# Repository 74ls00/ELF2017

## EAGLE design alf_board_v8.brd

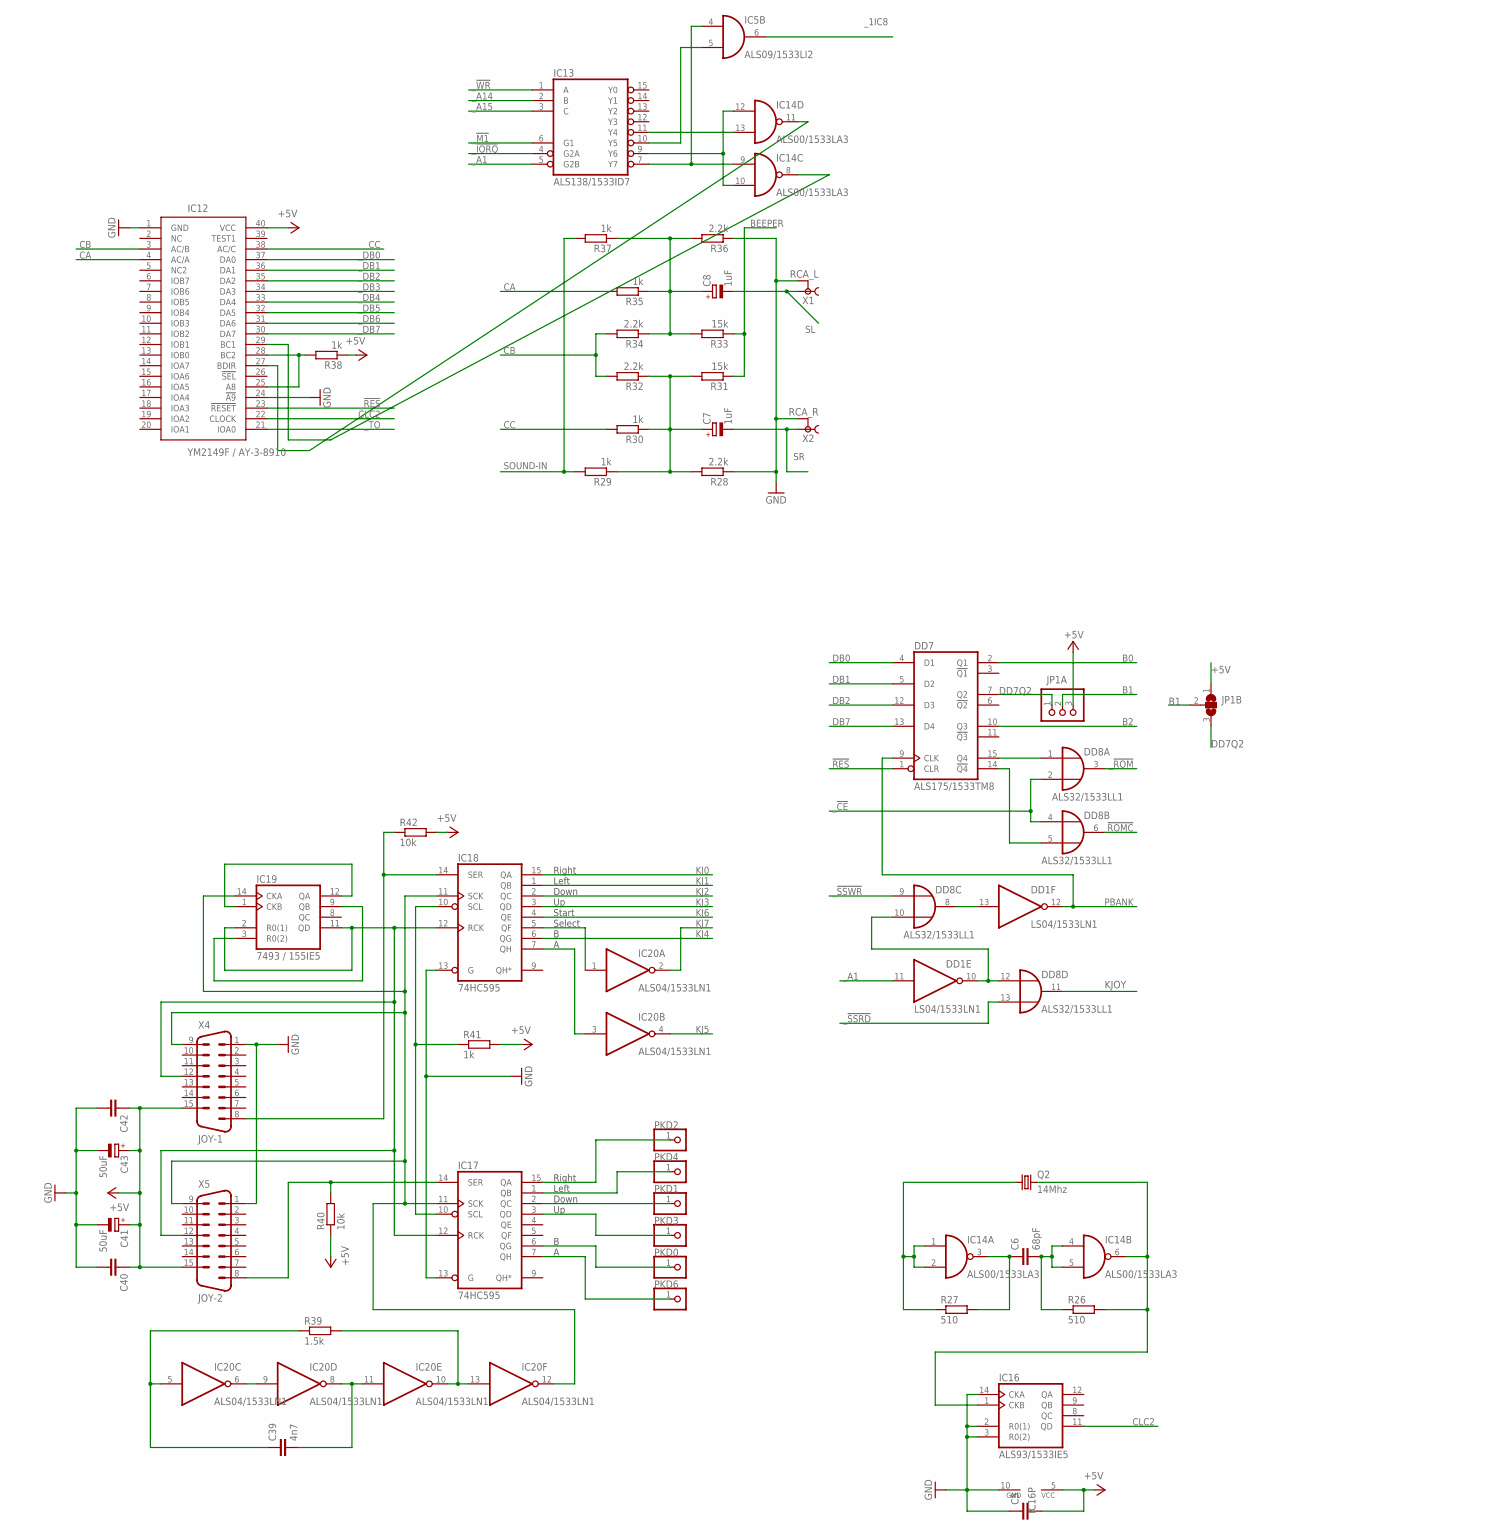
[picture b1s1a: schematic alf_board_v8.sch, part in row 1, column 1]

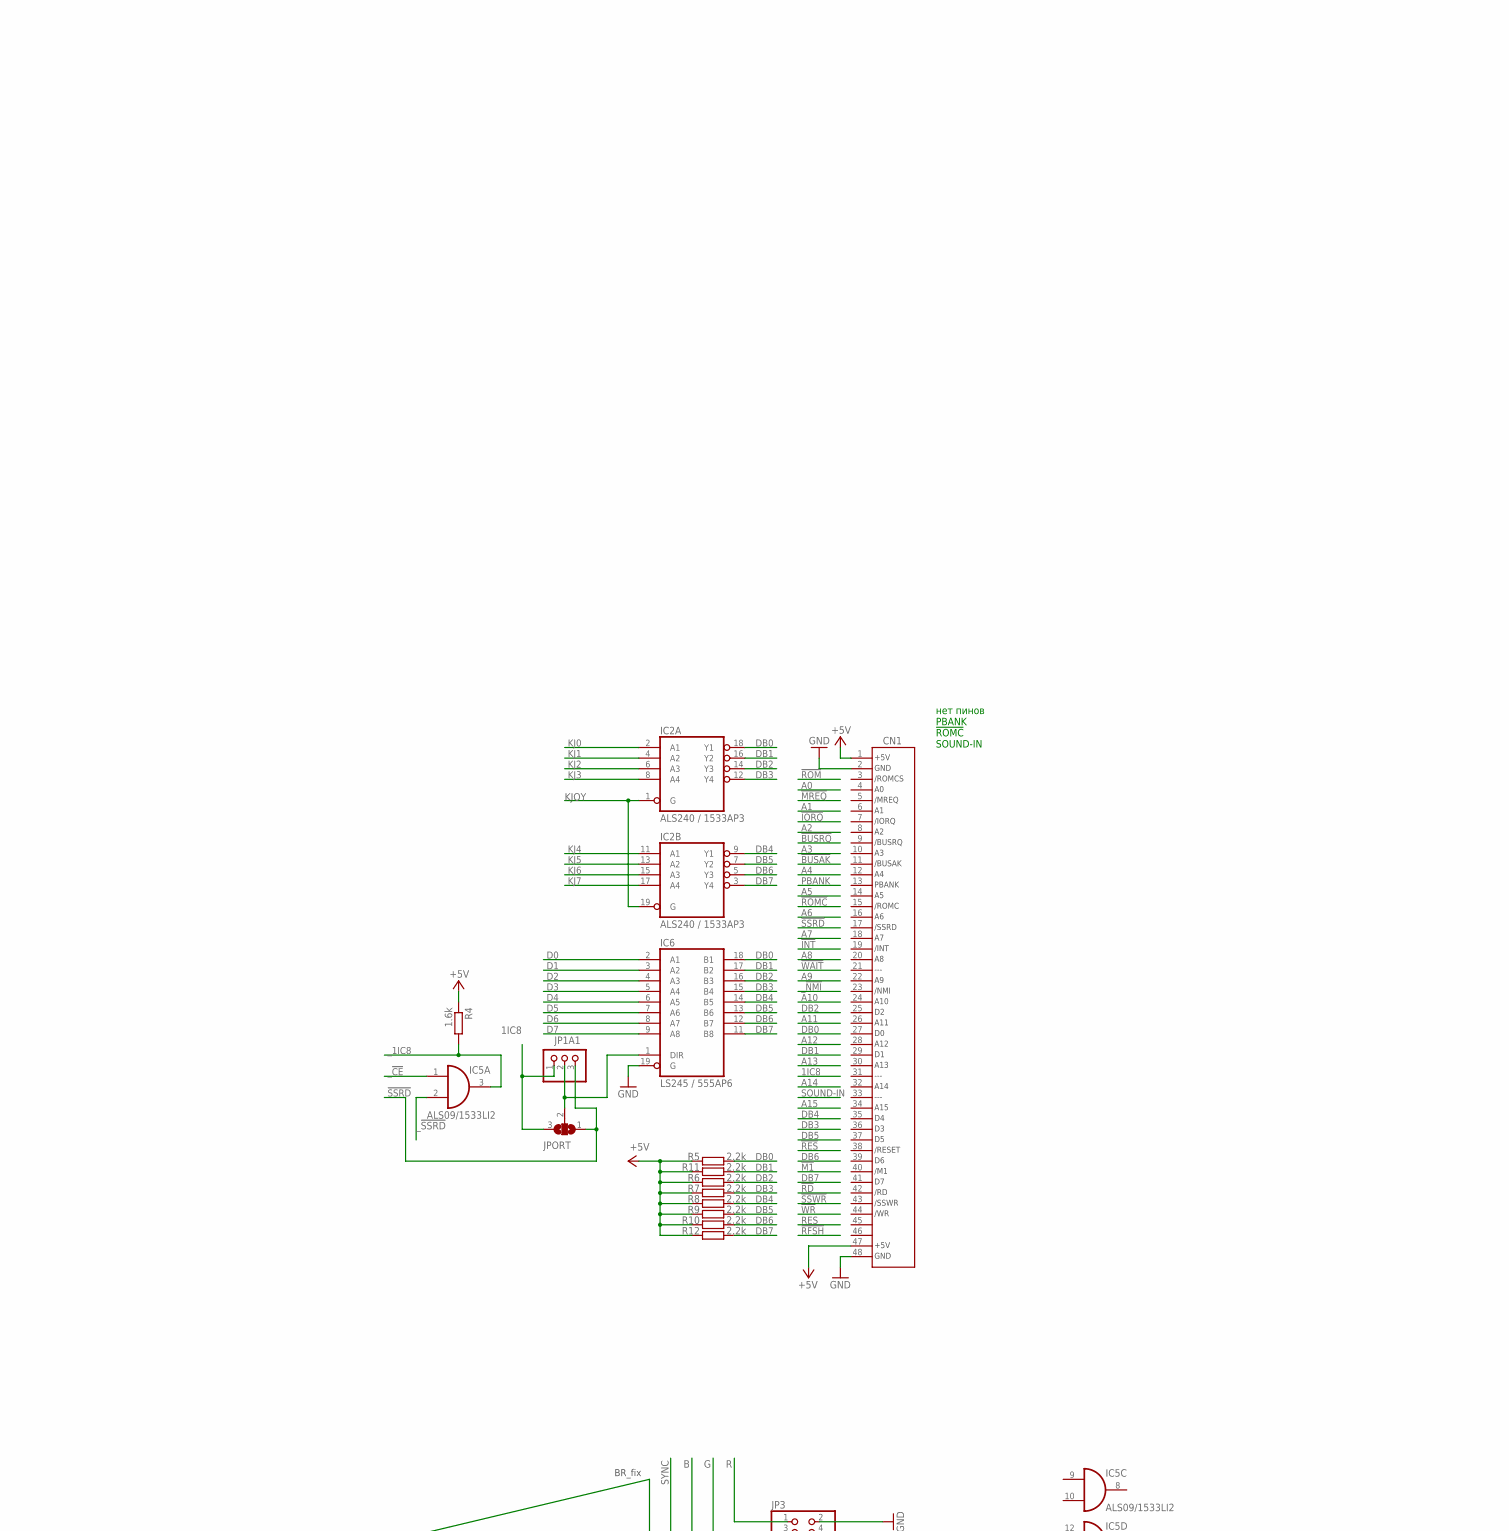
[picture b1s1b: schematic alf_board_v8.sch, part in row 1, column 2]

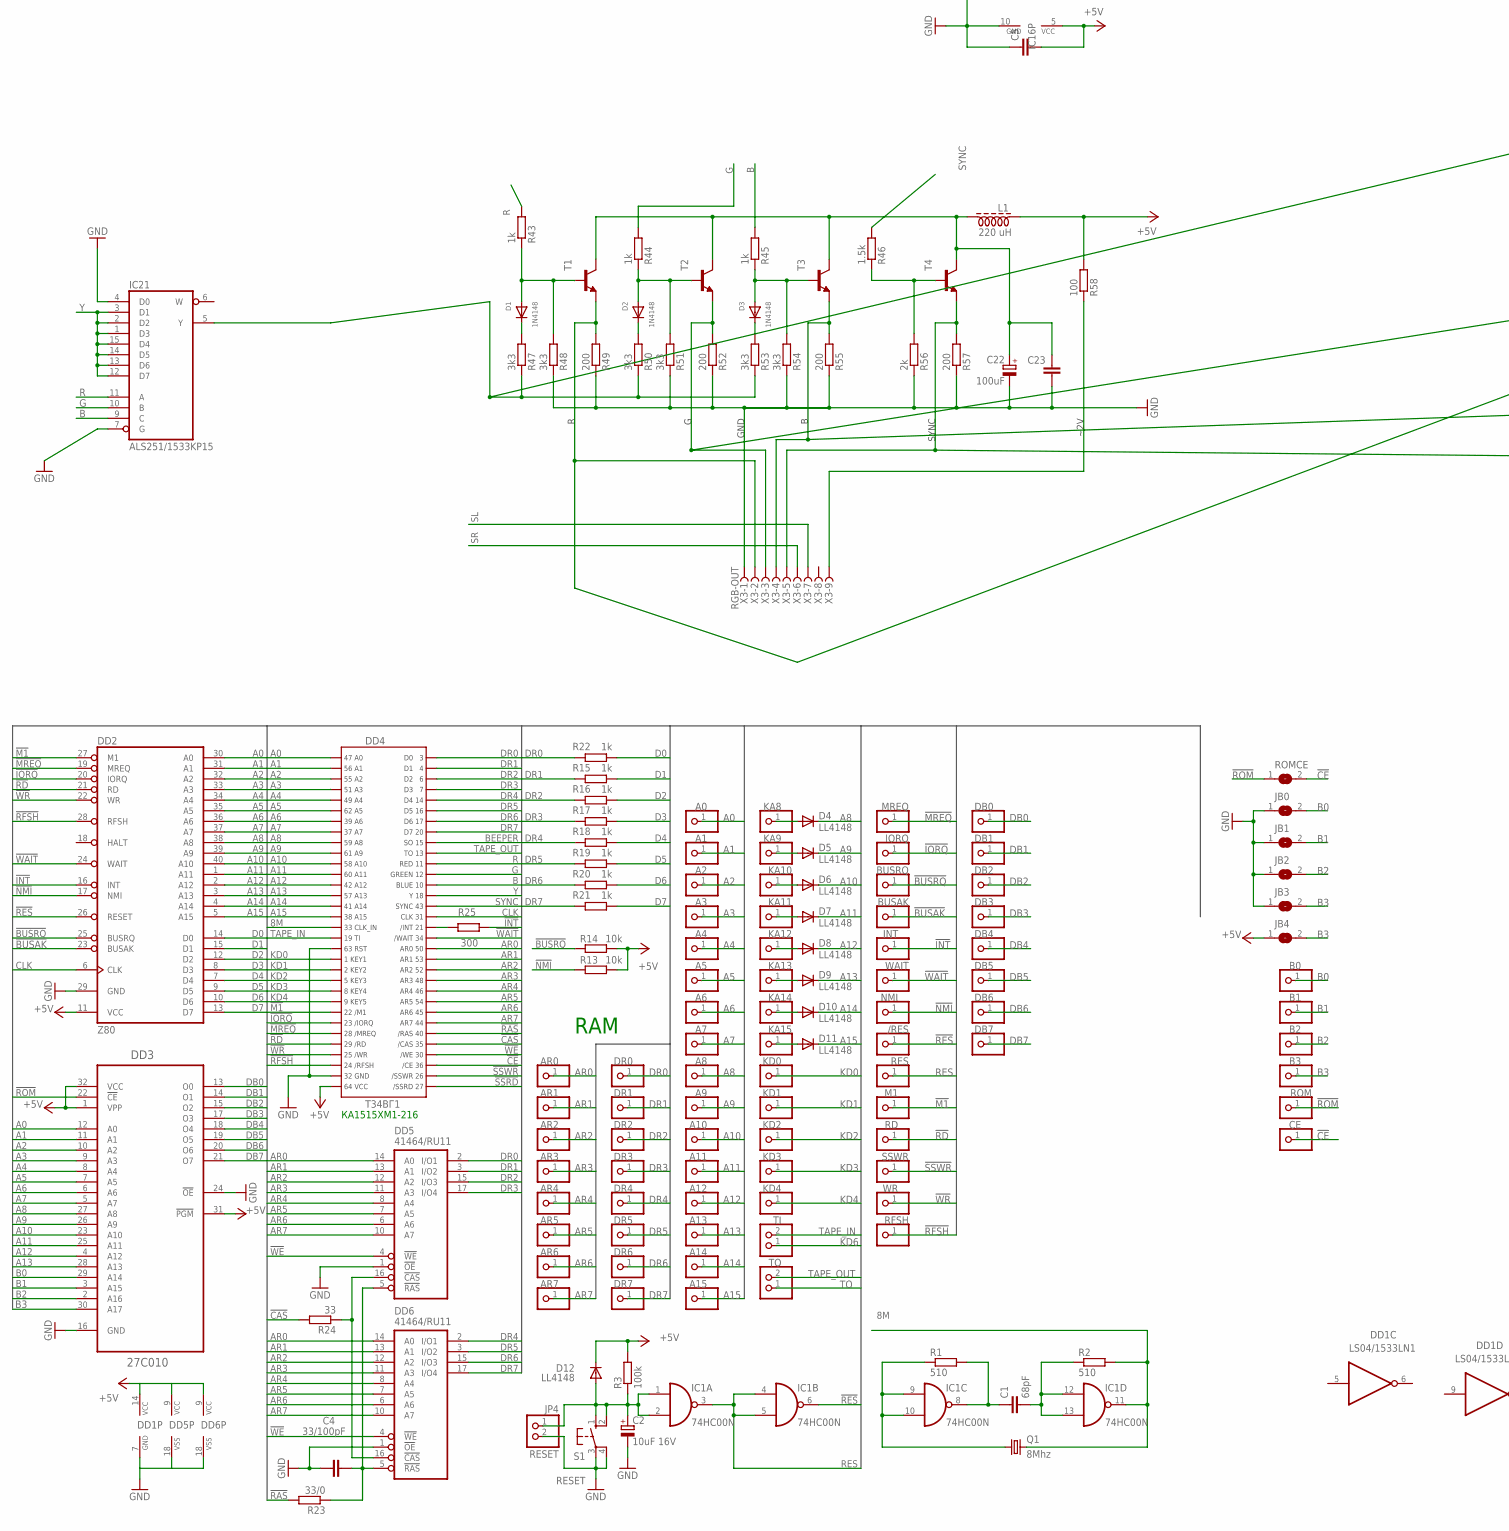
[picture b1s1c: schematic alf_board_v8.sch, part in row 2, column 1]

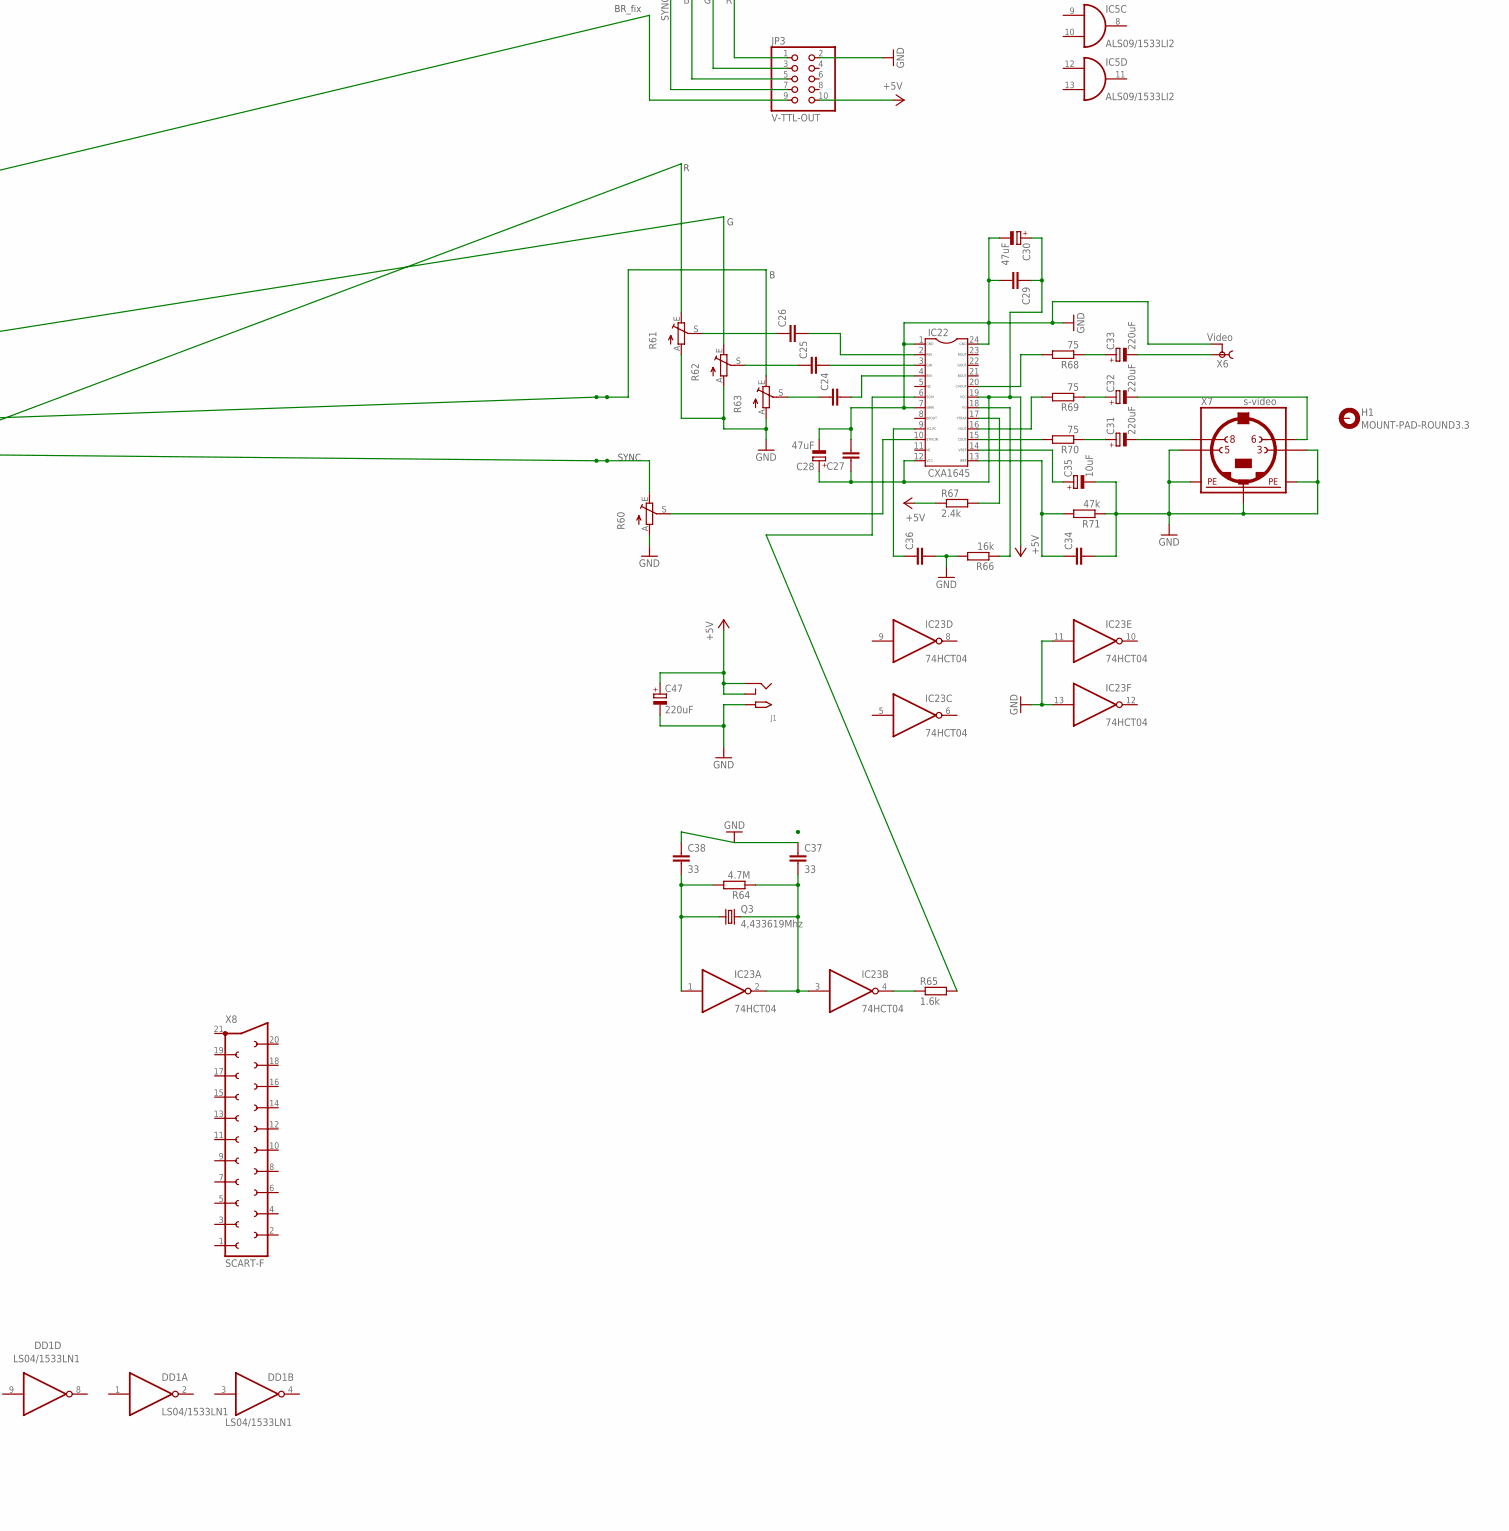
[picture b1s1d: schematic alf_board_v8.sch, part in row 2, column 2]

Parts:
/RES: PINHD-1X1; 1X01
A0, A1, A2, A3, A4, A5, A6, A7, A8, A9, A10, A11, A12, A13, A14, A15: PINHD-1X1; 1X01
AR0, AR1, AR2, AR3, AR4, AR5, AR6, AR7: PINHD-1X1; 1X01
B0, B1, B2, B3: PINHD-1X1; 1X01
BUSAK: PINHD-1X1; 1X01
BUSRQ: PINHD-1X1; 1X01
C1, C6: 68pF; C0805
C2: 10uF 16V; SMC_A; MPN MCNP35V106M5X11
C4: 33/100pF; C102-043X133
C5, C23, C24, C25, C26, C27, C29, C34, C36, C40, C42: C-EUC0805; C0805
C7, C8: 1uF; SMC_A
C22: 100uF; SMC_B
C28, C30: 47uF; SMC_B
C31, C32, C33, C47: 220uF; SMC_D
C35: 10uF; SMC_A
C37, C38: 33; C0805
C39: 4n7; C0805
C41, C43: 50uF; SMC_B
CE: PINHD-1X1; 1X01
CN1: СНП15-48
D1, D2, D3: 1N4148; DO-1N4148
D4, D5, D6, D7, D8, D9, D10, D11, D12: LL4148; SOD80C
DB0, DB1, DB2, DB3, DB4, DB5, DB6, DB7: PINHD-1X1; 1X01
DD1: LS04/1533LN1; DIL14
DD2: Z80; DIL40
DD3: 27C010; DIP254P1524X482-32P; MPN AT27C020-90PU
DD4: Т34ВГ1; TQFP64-MF
DD5, DD6: 41464/RU11; DIL18
DD7: ALS175/1533TM8; DIL16
DD8: ALS32/1533LL1; DIL14
DR0, DR1, DR2, DR3, DR4, DR5, DR6, DR7: PINHD-1X1; 1X01
H1: MOUNT-PAD-ROUND3.3; 3,3-PAD
IC1: 74HC00N; DIL14
IC2: ALS240 / 1533AP3; DIL20
IC5: ALS09/1533LI2; DIL14
IC6: LS245 / 555AP6; SO20W
IC12: YM2149F / AY-3-8910; DIL40
IC13: ALS138/1533ID7; DIL16
IC14: ALS00/1533LA3; DIL14
IC16: ALS93/1533IE5; DIL14
IC17, IC18: 74HC595; DIL16
IC19: 7493 / 155IE5; DIL14
IC20: ALS04/1533LN1; DIL14
IC21: ALS251/1533KP15; DIL16
IC22: CXA1645; SOP24
IC23: 74HCT04; DIL14
INT: PINHD-1X1; 1X01
IORQ: PINHD-1X1; 1X01
J1: 2.1MMJACKTHM; PJ-102A
JB0, JB1, JB2, JB3, JB4: SJ
JP1A, JP1A1: PINHD-1X3; 1X03
JP1B: SJ2W; SJ_2
JP3: V-TTL-OUT; 2X05
JP4: RESET; 1X02
JPORT: SJ2W; SJ_2
KA8, KA9, KA10, KA11, KA12, KA13, KA14, KA15: PINHD-1X1; 1X01
KD0, KD1, KD2, KD3, KD4: PINHD-1X1; 1X01
L1: 220 uH; Z27/24
M1: PINHD-1X1; 1X01
MREQ: PINHD-1X1; 1X01
NMI: PINHD-1X1; 1X01
PKD0, PKD1, PKD2, PKD3, PKD4, PKD6: PINHD-1X1; 1X01
Q1: 8Mhz; HC49/S; MPN HC49SM-3.6864-30-50-60-16-ATF
Q2: 14Mhz; HC49/S; MPN HC49SM-3.6864-30-50-60-16-ATF
Q3: 4,433619Mhz; HC49/S; MPN HC49SM-3.6864-30-50-60-16-ATF
R1, R2, R26, R27: 510; R0805
R3: 100k; R0805
R4, R65: 1.6k; R0805
R5, R6, R7, R8, R9, R10, R11, R12, R28, R32, R34, R36: 2.2k; R0805
R13, R14, R40, R42: 10k; R0805
R15, R16, R17, R18, R19, R20, R21, R22, R29, R30, R35, R37, R38, R41, R43, R44, R45: 1k; R0805
R23: 33/0; 0207/12
R24: 33; 0207/10
R25: 300; R0805
R31, R33: 15k; R0805
R39, R46: 1.5k; R0805
R47, R48, R50, R51, R53, R54: 3k3; R0805
R49, R52, R55, R57: 200; R0805
R56: 2k; R0805
R58: 100; R0805
R60, R61, R62, R63: TRIM_EU-CA6V; CA6V
R64: 4.7M; R0805
R66: 16k; R0805
R67: 2.4k; R0805
R68, R69, R70: 75; R0805
R71: 47k; R0805
RD: PINHD-1X1; 1X01
RES: PINHD-1X1; 1X01
RFSH: PINHD-1X1; 1X01
ROM: PINHD-1X1; 1X01
ROMCE: SJ
S1: RESET; B3F-10XX
SSWR: PINHD-1X1; 1X01
T1, T2, T3, T4: BC549-NPN-TO92-CBE; TO92-CBE
TI: PINHD-1X2; 1X02
TO: PINHD-1X2; 1X02
WAIT: PINHD-1X1; 1X01
WR: PINHD-1X1; 1X01
X1: RCA_L; TOBU3
X2: RCA_R; TOBU3
X3: RGB-OUT; H5M09RA
X4: JOY-1; M15HP
X5: JOY-2; M15HP
X6: Video; TOBU3
X7: s-video; M_DIN4
X8: SCART-F

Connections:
1IC8: JP1A1.1, JPORT.3
8M: DD4.33, IC1.11 (O), Q1.2, R2.2
!BUSAK: BUSAK.1, DD2.23 (BUSAK)
!BUSRQ: BUSRQ.1, DD2.25 (BUSRQ), R14.2
!CAS: DD4.35, R24.2
!CE: CE.1, DD4.36, ROMCE.2
!INT: DD2.16 (INT), INT.1, R25.2
!IORQ: DD2.20 (IORQ), DD4.23, IORQ.1
!M1: DD2.27 (M1), DD4.22, M1.1
!MREQ: DD2.19 (MREQ), DD4.28, MREQ.1
!NMI: DD2.17 (NMI), NMI.1, R13.2
!RAS: DD4.40, R23.2
!RD: DD2.21 (RD), DD4.29, RD.1
!RES: /RES.1, DD2.26 (RESET), DD7.1 (CLR), IC1.6 (O)
!RFSH: DD2.28 (RFSH), DD4.24, RFSH.1
!ROM: DD3.22 (!CE), ROM.1, ROMCE.1
!ROMC: DD8.6 (O)
!SSRD: DD4.27, JP1A1.3, JPORT.1
!SSWR: DD4.26, SSWR.1
!WAIT: DD2.24 (WAIT), DD4.34, WAIT.1
!WE: DD4.30, DD5.4 (!WE), DD6.4 (!WE)
!WR: DD2.22 (WR), DD4.25, WR.1
+5V: C5.2, C27.1, C28.+, C29.1, C30.+, C40.1, C41.+, C42.1, C43.+, C47.+, CN1.1, CN1.47, D12.C, DD1.14 (VCC), DD2.11 (VCC), DD3.1 (VPP), DD3.31 (!PGM), DD3.32 (VCC), DD4.64, DD5.9 (VCC), DD6.9 (VCC), IC12.40 (VCC), IC16.5 (VCC), IC22.12, IC22.19, J1.RING, J1.RING_SW, JB4.1, JP1A.3, JP1B.1, JP3.10, L1.1, R3.2, R4.1, R5.1, R6.1, R7.1, R8.1, R9.1, R10.1, R11.1, R12.1, R13.1, R14.1, R38.1, R40.1, R41.2, R42.2, R58.2, R67.1, X4.15, X5.15
A0: A0.1, DD2.30 (A0), DD3.12 (A0), DD4.47
A1: A1.1, DD2.31 (A1), DD3.11 (A1), DD4.56
A2: A2.1, DD2.32 (A2), DD3.10 (A2), DD4.55
A3: A3.1, DD2.33 (A3), DD3.9 (A3), DD4.51
A4: A4.1, DD2.34 (A4), DD3.8 (A4), DD4.49
A5: A5.1, DD2.35 (A5), DD3.7 (A5), DD4.62
A6: A6.1, DD2.36 (A6), DD3.6 (A6), DD4.39
A7: A7.1, DD2.37 (A7), DD3.5 (A7), DD4.37
A8: A8.1, D4.C, DD2.38 (A8), DD3.27 (A8), DD4.59
A9: A9.1, D5.C, DD2.39 (A9), DD3.26 (A9), DD4.61
A10: A10.1, D6.C, DD2.40 (A10), DD3.23 (A10), DD4.58
A11: A11.1, D7.C, DD2.1 (A11), DD3.25 (A11), DD4.60
A12: A12.1, D8.C, DD2.2 (A12), DD3.4 (A12), DD4.42
A13: A13.1, D9.C, DD2.3 (A13), DD3.28 (A13), DD4.57
A14: A14.1, D10.C, DD2.4 (A14), DD4.41
A15: A15.1, D11.C, DD2.5 (A15), DD4.38
AR0: AR0.1, DD4.50, DD5.14 (A0), DD6.14 (A0)
AR1: AR1.1, DD4.53, DD5.13 (A1), DD6.13 (A1)
AR2: AR2.1, DD4.52, DD5.12 (A2), DD6.12 (A2)
AR3: AR3.1, DD4.48, DD5.11 (A3), DD6.11 (A3)
AR4: AR4.1, DD4.46, DD5.8 (A4), DD6.8 (A4)
AR5: AR5.1, DD4.54, DD5.7 (A5), DD6.7 (A5)
AR6: AR6.1, DD4.45, DD5.6 (A6), DD6.6 (A6)
AR7: AR7.1, DD4.44, DD5.10 (A7), DD6.10 (A7)
B: DD4.10, IC21.9 (C), JP3.5, R45.2
B0: B0.1, DD3.29 (A14), DD7.2 (Q1), JB0.2
B1: B1.1, DD3.3 (A15), JB1.2, JP1A.2, JP1B.2
B2: B2.1, DD3.2 (A16), DD7.10 (Q3), JB2.2
B3: B3.1, DD3.30 (A17), JB3.2, JB4.2
BEEPER: DD4.15, R31.1, R33.1
CA: IC12.4 (AC/A), R35.2
CAS_RAM: DD5.16 (!CAS), DD6.16 (!CAS), R24.1
CB: IC12.3 (AC/B), R32.2, R34.2
CC: IC12.38 (AC/C), R30.2
CLC2: IC12.22 (CLOCK), IC16.11 (QD)
CLK: DD2.6 (CLK), DD4.31
D0: DD2.14 (D0), IC6.2 (A1), R22.1
D1: DD2.15 (D1), IC6.3 (A2), R15.1
D2: DD2.12 (D2), IC6.4 (A3), R16.1
D3: DD2.8 (D3), IC6.5 (A4), R17.1
D4: DD2.7 (D4), IC6.6 (A5), R18.1
D5: DD2.9 (D5), IC6.7 (A6), R19.1
D6: DD2.10 (D6), IC6.8 (A7), R20.1
D7: DD2.13 (D7), IC6.9 (A8), R21.1
DB0: DB0.1, DD3.13 (O0), DD7.4 (D1), IC2.18 (Y1), IC6.18 (B1), R5.2
DB1: DB1.1, DD3.14 (O1), DD7.5 (D2), IC2.16 (Y2), IC6.17 (B2), R11.2
DB2: DB2.1, DD3.15 (O2), DD7.12 (D3), IC2.14 (Y3), IC6.16 (B3), R6.2
DB3: DB3.1, DD3.17 (O3), IC2.12 (Y4), IC6.15 (B4), R7.2
DB4: DB4.1, DD3.18 (O4), IC2.9 (Y1), IC6.14 (B5), R8.2
DB5: DB5.1, DD3.19 (O5), IC2.7 (Y2), IC6.13 (B6), R9.2
DB6: DB6.1, DD3.20 (O6), IC2.5 (Y3), IC6.12 (B7), R10.2
DB7: DB7.1, DD3.21 (O7), DD7.13 (D4), IC2.3 (Y4), IC6.11 (B8), R12.2
DD7Q2: DD7.7 (Q2), JP1A.1, JP1B.3
DR0: DD4.3, DD5.2 (I/O1), DR0.1, R22.2
DR1: DD4.4, DD5.3 (I/O2), DR1.1, R15.2
DR2: DD4.6, DD5.15 (I/O3), DR2.1, R16.2
DR3: DD4.7, DD5.17 (I/O4), DR3.1, R17.2
DR4: DD4.14, DD6.2 (I/O1), DR4.1, R18.2
DR5: DD4.16, DD6.3 (I/O2), DR5.1, R19.2
DR6: DD4.17, DD6.15 (I/O3), DR6.1, R20.2
DR7: DD4.20, DD6.17 (I/O4), DR7.1, R21.2
G: DD4.12, IC21.10 (B), JP3.3, R44.2
GND: C2.-, C4.1, C5.1, C22.-, C23.2, C27.2, C28.-, C29.2, C30.-, C34.2, C35.-, C36.2, C37.1, C38.1, C40.2, C41.-, C42.2, C43.-, C47.-, CN1.2, CN1.48, DD1.7 (GND), DD2.29 (GND), DD3.16 (GND), DD3.24 (!OE), DD4.32, DD4.63, DD5.1 (!OE), DD5.18 (VSS), DD6.1 (!OE), DD6.18 (VSS), DD7.8 (GND), DD8.7 (GND), IC1.7 (GND), IC2.10 (GND), IC5.7 (GND), IC6.10 (GND), IC6.19 (G), IC12.1 (GND), IC12.24 (!A9), IC13.8 (GND), IC14.7 (GND), IC16.2 (R0(1)), IC16.3 (R0(2)), IC16.10 (GND), IC16.14 (CKA), IC17.8 (GND), IC17.13 (G), IC18.8 (GND), IC18.13 (G), IC19.10 (GND), IC20.7 (GND), IC21.4 (D0), IC21.7 (G), IC21.8 (GND), IC22.1, IC22.7, IC22.24, IC23.7 (GND), IC23.11 (I), IC23.13 (I), J1.TIP, JB0.1, JB1.1, JB2.1, JB3.1, JP3.2, JP4.2, R28.1, R36.1, R48.1, R49.1, R51.1, R52.1, R54.1, R55.1, R56.1, R57.1, R60.A, R61.A, R62.A, R63.A, R66.2, R71.1, S1.3, S1.4 (P1), X1.2, X1.2@1 (2), X1.2@2 (2), X2.2, X2.2@1 (2), X2.2@2 (2), X3.1, X4.1, X5.1, X6.2, X6.2@1 (2), X6.2@2 (2), X7.3, X7.5, X7.SH1 (PE1), X7.SH2 (PE2), X7.SH3 (PE3)
KD0: DD4.1, KD0.1
KD1: DD4.2, KD1.1
KD2: DD4.5, KD2.1
KD3: DD4.8, KD3.1
KD4: DD4.9, KD4.1
KD6: TI.1
KJ0: IC2.2 (A1), IC18.15 (QA)
KJ1: IC2.4 (A2), IC18.1 (QB)
KJ2: IC2.6 (A3), IC18.2 (QC)
KJ3: IC2.8 (A4), IC18.3 (QD)
KJ4: IC2.11 (A1), IC18.6 (QG)
KJ5: IC2.13 (A2), IC20.4 (O)
KJ6: IC2.15 (A3), IC18.4 (QE)
KJ7: IC2.17 (A4), IC20.2 (O)
KJOY: DD8.11 (O), IC2.1 (G), IC2.19 (G)
unnamed: IC23.4 (O), R65.1
unnamed: C1.1, IC1.8 (O), R1.2
unnamed: C1.2, IC1.12 (I0), IC1.13 (I1), R2.1
unnamed: IC1.9 (I0), IC1.10 (I1), Q1.1, R1.1
unnamed: IC18.5 (QF), IC20.1 (I)
unnamed: IC18.7 (QH), IC20.3 (I)
unnamed: DD1.13 (I), DD8.8 (O)
unnamed: C2.+, D12.A, IC1.1 (I0), IC1.2 (I1), JP4.1, R3.1, S1.1 (S), S1.2 (S1)
unnamed: D4.A, KA8.1
unnamed: DD1.10 (O), DD8.10 (I1), DD8.12 (I0)
unnamed: DD7.14 (!Q4), DD8.5 (I1)
unnamed: DD7.15 (Q4), DD8.1 (I0)
unnamed: IC17.12 (RCK), IC18.12 (RCK), IC19.2 (R0(1)), IC19.11 (QD), X4.12, X5.12
unnamed: IC17.7 (QH), PKD6.1
unnamed: IC12.25 (A8), IC12.28 (BC2), R38.2
unnamed: D1.A, R43.1, R48.2, T1.B
unnamed: D1.C, R47.2
unnamed: R49.2, R61.E, T1.E, X3.2
unnamed: D2.A, R44.1, R51.2, T2.B
unnamed: D2.C, R50.2
unnamed: R52.2, R62.E, T2.E, X3.3
unnamed: IC22.17, R67.2
unnamed: IC12.27 (BDIR), IC14.11 (O)
unnamed: IC5.4 (I0), IC13.7 (Y7), IC14.9 (I0)
unnamed: IC13.11 (Y4), IC14.13 (I1)
unnamed: IC5.5 (I1), IC13.10 (Y5)
unnamed: IC13.9 (Y6), IC14.10 (I1), IC14.12 (I0)
unnamed: IC17.10 (SCL), IC18.10 (SCL), R41.1
unnamed: IC12.29 (BC1), IC14.8 (O)
unnamed: C8.+, R33.2, R34.1, R35.1, R36.2, R37.1
unnamed: C7.+, R28.2, R29.1, R30.1, R31.2, R32.1
unnamed: D3.A, R45.1, R54.2, T3.B
unnamed: IC17.11 (SCK), IC18.11 (SCK), IC19.14 (CKA), IC20.12 (O), X4.9, X5.9
unnamed: C39.1, IC20.5 (I), R39.1
unnamed: IC14.6 (O), IC16.1 (CKB), Q2.2, R26.2
unnamed: IC14.1 (I0), IC14.2 (I1), Q2.1, R27.1
unnamed: C6.1, IC14.3 (O), R27.2
unnamed: C6.2, IC14.4 (I0), IC14.5 (I1), R26.1
unnamed: D3.C, R53.2
unnamed: R55.2, R63.E, T3.E, X3.4
unnamed: R57.2, R60.E, T4.E, X3.5
unnamed: C22.+, C23.1, L1.2, T1.C, T2.C, T3.C, T4.C
unnamed: R58.1, X3.9
unnamed: IC17.14 (SER), R40.2, X5.8
unnamed: IC19.3 (R0(2)), IC19.9 (QB)
unnamed: IC18.14 (SER), R42.1, X4.8
unnamed: IC19.1 (CKB), IC19.12 (QA)
unnamed: C39.2, IC20.8 (O), IC20.11 (I)
unnamed: IC20.10 (O), IC20.13 (I), R39.2
unnamed: C26.1, R61.S
unnamed: IC20.6 (O), IC20.9 (I)
unnamed: C25.1, R62.S
unnamed: C24.1, R63.S
unnamed: C25.2, IC22.3
unnamed: C26.2, IC22.2
unnamed: C24.2, IC22.4
unnamed: C38.2, IC23.1 (I), Q3.1, R64.2
unnamed: C37.2, IC23.2 (O), IC23.3 (I), Q3.2, R64.1
unnamed: IC22.10, R60.S
unnamed: IC21.5 (Y), JP3.9, R47.1, R50.1, R53.1
unnamed: IC22.6, R65.2
unnamed: IC22.20, R68.2
unnamed: C36.1, IC22.9
unnamed: IC22.18, R66.1
unnamed: IC22.16, R69.2
unnamed: IC22.15, R70.2
unnamed: C33.+, R68.1
unnamed: C32.+, R69.1
unnamed: C31.+, R70.1
unnamed: C35.+, IC22.14
unnamed: C34.1, IC22.13, R71.2
unnamed: C33.-, X6.1
unnamed: C32.-, X7.6
unnamed: C31.-, X7.8
unnamed: IC17.6 (QG), PKD0.1
unnamed: D5.A, KA9.1
unnamed: D6.A, KA10.1
unnamed: D7.A, KA11.1
unnamed: D8.A, KA12.1
unnamed: D9.A, KA13.1
unnamed: D10.A, KA14.1
unnamed: D11.A, KA15.1
unnamed: IC6.1 (DIR), JP1A1.2, JPORT.2
unnamed: R46.1, R56.2, T4.B
unnamed: IC17.3 (QD), PKD3.1
unnamed: IC17.2 (QC), PKD1.1
unnamed: IC17.15 (QA), PKD2.1
unnamed: IC17.1 (QB), PKD4.1
PBANK: DD1.12 (O), DD7.9 (CLK)
R: DD4.11, IC21.11 (A), JP3.1, R43.2
RAS_RAM: C4.2, DD5.5 (!RAS), DD6.5 (!RAS), R23.1
RES: IC1.3 (O), IC1.4 (I0), IC1.5 (I1), RES.1
R_INT: DD4.21, R25.1
SL: C8.-, X1.1, X3.7
SOUND-IN: R29.2, R37.2
SR: C7.-, X2.1, X3.6
SYNC: DD4.43, JP3.7, R46.2
TAPE_IN: DD4.19, TI.2
TAPE_OUT: DD4.13, TO.2
TO: TO.1
VCC: DD7.16 (VCC), DD8.14 (VCC), IC1.14 (VCC), IC2.20 (VCC), IC5.14 (VCC), IC6.20 (VCC), IC13.16 (VCC), IC14.14 (VCC), IC17.16 (VCC), IC18.16 (VCC), IC19.5 (VCC), IC20.14 (VCC), IC21.16 (VCC), IC23.14 (VCC)
Y: DD4.18, IC21.1 (D3), IC21.2 (D2), IC21.3 (D1), IC21.12 (D7), IC21.13 (D6), IC21.14 (D5), IC21.15 (D4)
_1IC8: IC5.3 (O), IC5.6 (O), R4.2
_!CE: DD8.2 (I1), DD8.4 (I0), IC5.1 (I0)
_!IORQ: IC13.4 (G2A)
_!M1: IC13.6 (G1)
_!RES: IC12.23 (!RESET)
_!ROM: DD8.3 (O)
_!SSRD: DD8.13 (I1), IC5.2 (I1)
_!SSWR: DD8.9 (I0)
_!WR: IC13.1 (A)
_A1: DD1.11 (I), IC13.5 (G2B)
_A14: IC13.2 (B)
_A15: IC13.3 (C)
_DB0: IC12.37 (DA0)
_DB1: IC12.36 (DA1)
_DB2: IC12.35 (DA2)
_DB3: IC12.34 (DA3)
_DB4: IC12.33 (DA4)
_DB5: IC12.32 (DA5)
_DB6: IC12.31 (DA6)
_DB7: IC12.30 (DA7)
_TO: IC12.21 (IOA0)

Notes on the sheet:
SYNC
GND
~2V
Right
Left
Down
Start
Select
BR_fix
RAM
нет пинов PBANK !ROMC SOUND-IN
КА1515ХМ1-216

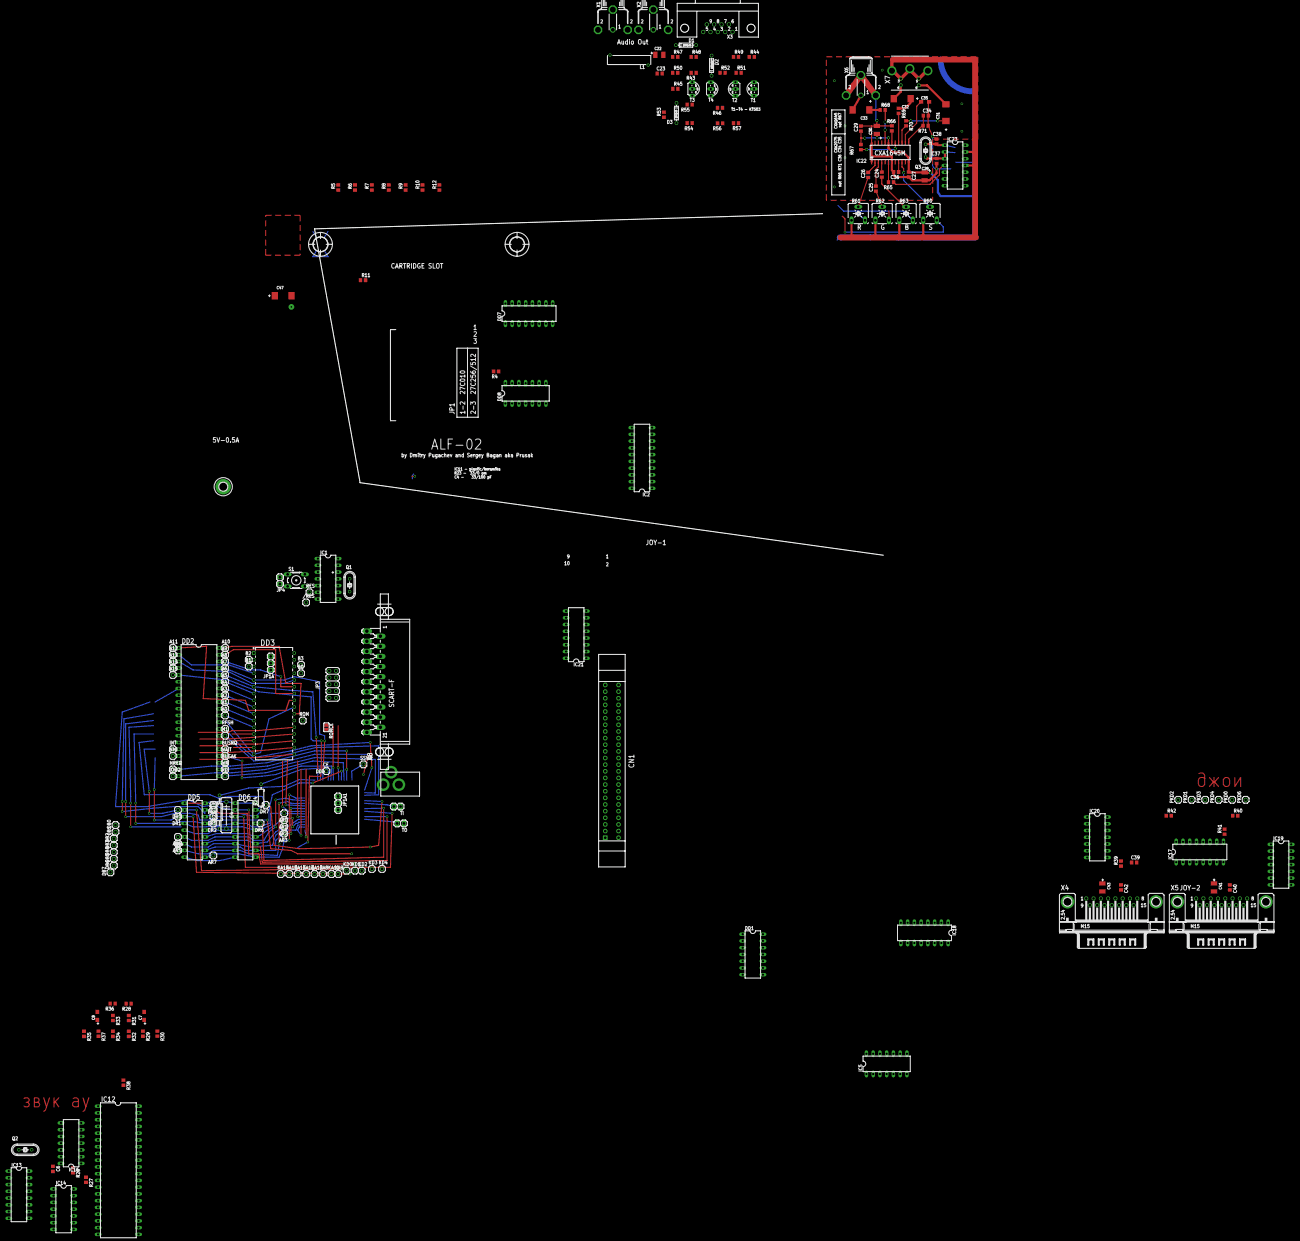
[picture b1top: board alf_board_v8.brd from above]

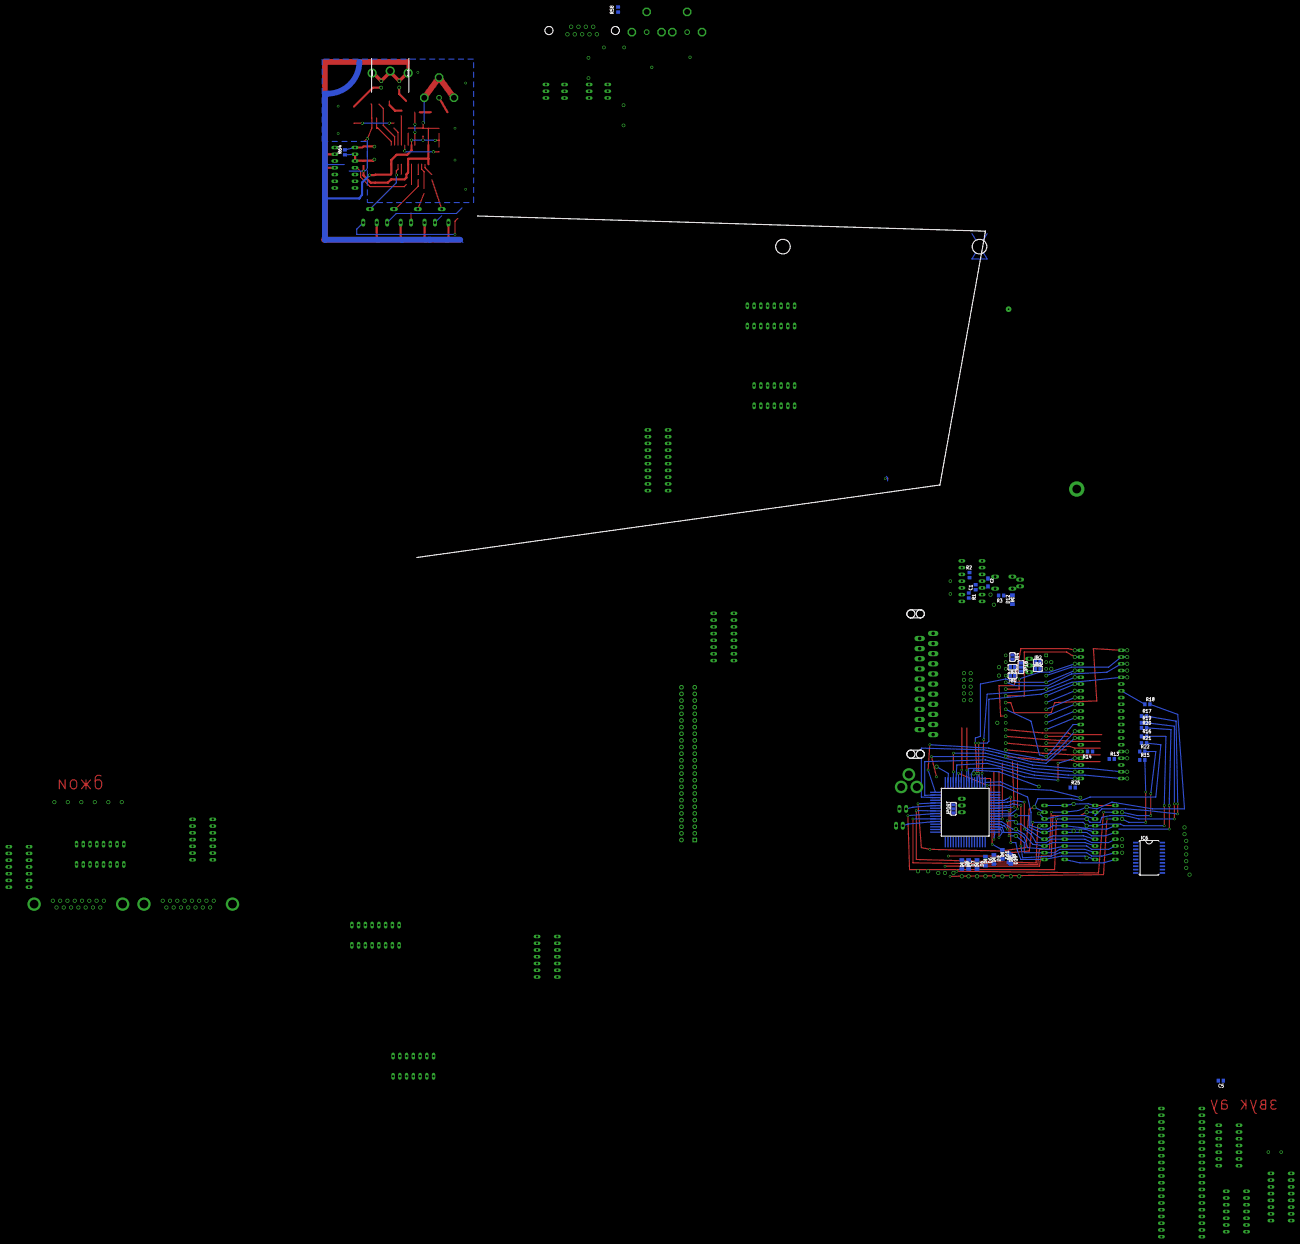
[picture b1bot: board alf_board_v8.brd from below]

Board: 2 copper layers, 250 parts (36 on the bottom side), 204 nets.

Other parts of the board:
U$2, U$3: 5,5

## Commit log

2017-11-07 vil0
